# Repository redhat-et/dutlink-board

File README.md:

# jumpstarter
jumpstarter is a project designed to enable generic Hardware in the Loop testability for Edge / embedded designs.

# Software Agent

Should enable standard CI tools and pipeline systems (tekton, gitlab, github, Jenkins, etc...) to integrate with the hardware:
 * Load a device image
 * Reboot
 * Gather logs and wait for finish
 * Return results to the CI system
 * Capture power profile during the whole device lifecycle.

# Hardware Agent
One of the components of the project is an Open Hardware board that bridges the Software and Hardware world
of Edge customers. Enabling them to perform Continous Integration of their Hardware and Software.

It's designed to be mounted on 1U 19" Server racks, in the MiniITX format, and should be connected to an
agent that will perform the control loop on the Device Under Test.

## Features

* USB Storage sharing
  * A storage device can be connected to the Testing host, and then passed down to the DUT
  * USB3.1 (up to 10Gbps) capable
  * USB3.0 and 2.0 capable for backwards compatibility
  * Storage device power cycling

* DUT Power management:
  * ON/OFF, Reset, Reboot
  * Measurement and logging in watts (Integration to Kepler)
  * 5-25V power supply support
  * USB-PD power supply support 5-20V with DUT power negotiation
 
* DUT Control (3.3v I/O)
  * UART Serial port TX/RX (for logging and tracing)
  * 4 customizable control signals
  * RESET signal

# Images of release 1.0.0, on prototyping stage

Yes, we are optimistic with versioning!

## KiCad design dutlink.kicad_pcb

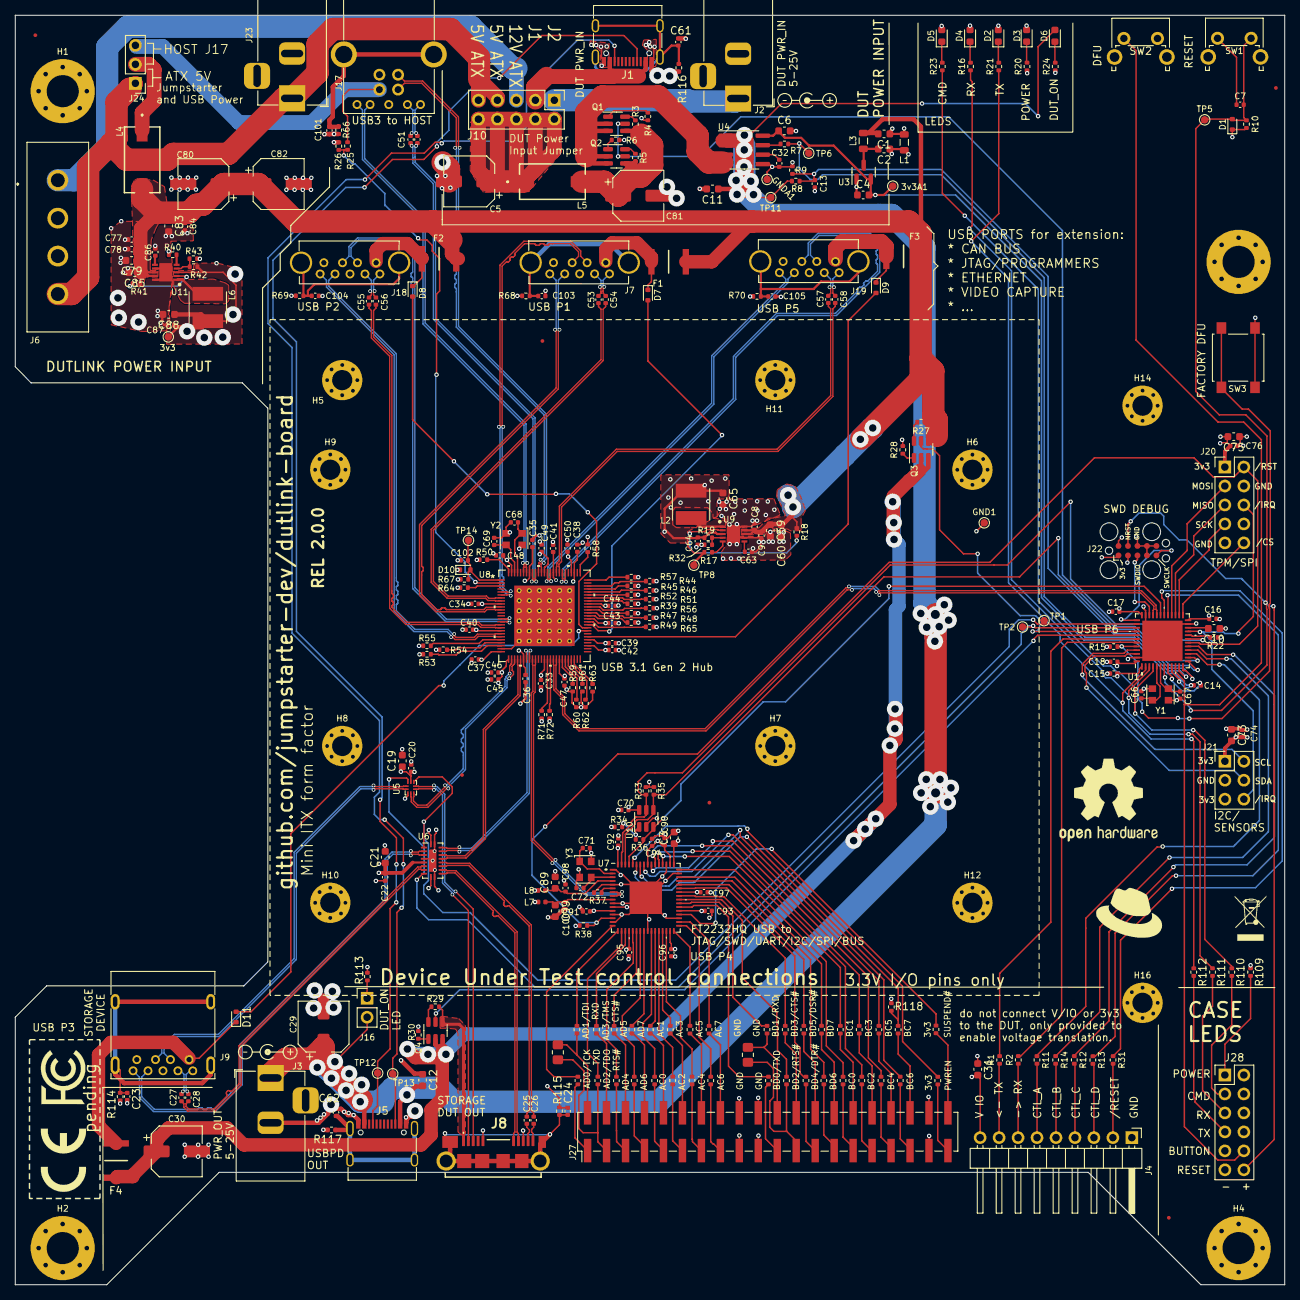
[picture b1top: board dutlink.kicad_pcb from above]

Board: 4 copper layers, 170.0 x 170.0 mm, 320 parts (0 on the bottom side), 273 nets.

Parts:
3v1, 3v3A1: TestPoint; TestPoint_Pad_D1.0mm
C1, C2, C4, C6, C11, C12, C19, C21, C31, C73, C75, C83: 1uF; C_0603_1608Metric
C3: 3.3uF; C_0603_1608Metric
C5, C29, C30, C80, C81, C82: 47uF 32V; CP_Elec_6.3x5.4_Nichicon
C7, C8, C9, C13, C14, C15, C16, C17, C18, C20, C22, C23, C24, C25, C26, C27, C28, C33, C34, C35, C36, C37, C38, C39, C40, C41, C42, C43, C44, C45, C46, C47, C48, C49, C50, C51, C52, C53, C54, C55, C56, C57, C58, C61, C62, C64, C70, C74, C76, C77, C78, C84, C87, C90, C91, C92, C93, C94, C95, C96, C97, C98, C100, C101, C102, C103, C104, C105: 100nF; C_0402_1005Metric
C10, C60, C85: 2.2uF; C_0603_1608Metric
C32: 1nF; C_0402_1005Metric
C59, C65, C79, C88: 22uF; C_0603_1608Metric
C63, C86: 470pF; C_0402_1005Metric
C66, C67, C68, C69: 12pF; C_0402_1005Metric
C71, C72: 27pF; C_0402_1005Metric
C89, C99: 4.7uF; C_0603_1608Metric
D1, D10: 1N4148WT; D_SOD-523
D2, D3, D4, D5, D6: LED; LED_0603_1608Metric
D7, D8, D9, D11: 1N4448WT; D_SOD-523
F1, F2, F3, F4: MF-MSMF125-2
FID1, FID2, FID3, FID4, FID5, FID6: Fiducial; Fiducial_0.5mm_Mask1mm
GND1: TestPoint; TestPoint_Pad_D1.0mm
GNDA1: TestPoint; TestPoint_Pad_D1.0mm
H1, H2, H3, H4: ITX MountingHole; MountingHole_4.3mm_M4_Pad_Via
H5, H6, H7, H8, H9, H10, H11, H12, H14, H16: Board MountingHole; MountingHole_2.7mm_M2.5_Pad_Via
J1, J5: USB_C_Receptacle_PowerOnly_6P; USB_C_Receptacle_G-Switch_GT-USB-7010ASV_fix
J2, J3: Barrel_Jack_MountingPin; BarrelJack_Horizontal
J4: Conn_01x09_Pin; PinHeader_1x09_P2.54mm_Horizontal
J6: Molex 4 Pin Peripheral Power Connector; 3502111
J7, J18, J19: USB3_A; SS-52000-004
J8: Hirose USB3_B_Micro; ZX360DB10P30
J9: USB3_A; USB3_A_Molex_48393-001
J10, J20: SPI/TPM connector; PinHeader_2x05_P2.54mm_Vertical
J16: Conn_01x02_Pin; PinHeader_1x02_P2.54mm_Vertical
J17: USB3_B; Wurth WR-COM USB 3.0 692221030100
J21: I2C connector; PinHeader_2x03_P2.54mm_Vertical
J22: NC; Tag-Connect_TC2050-IDC-FP_2x05_P1.27mm_Vertical
J23: DNM; BarrelJack_Horizontal
J24: Conn_01x03_Pin; PinHeader_1x03_P2.54mm_Vertical
J27: Conn_02x20_Odd_Even; PinHeader_2x20_P2.54mm_Vertical_SMD
J28: 6x2 2.54mm header; PinHeader_2x06_P2.54mm_Vertical
L1, L3: 10uH; L_0805_2012Metric
L2, L6: 1.5uH; LQH5BPB100MT0L
L4, L5: 7427932
L7, L8: 120Ω@100MH; L_0402_1005Metric
Q1, Q2, Q3, Q4: FDC6330L; TSOT-23-6
R1, R2, R7: 50; R_0402_1005Metric
R3, R5, R27, R29: 47k; R_0402_1005Metric
R4, R6, R28, R30: 2k2; R_0402_1005Metric
R8: 2k4 1%; R_0402_1005Metric
R9: 470 1%; R_0402_1005Metric
R10, R15, R17, R18, R19, R22, R33, R34, R35, R39, R40, R41, R44, R45, R46, R47, R48, R49, R55, R56, R57, R58, R65, R67: 10k; R_0402_1005Metric
R11, R12, R13, R14, R31, R73, R74, R75, R76, R77, R78, R79, R80, R81, R82, R83, R84, R85, R86, R87, R88, R89, R90, R91, R92, R93, R94, R95, R96, R97, R98, R99, R100, R101, R102, R103, R104, R105, R106: 100; R_0402_1005Metric
R16, R20, R21, R23, R109, R110, R111, R112: 470; R_0402_1005Metric
R24, R36, R38, R113: 2k; R_0402_1005Metric
R25: 43K; R_0402_1005Metric
R26: 49K9 1%; R_0402_1005Metric
R32, R37, R50: 12k 1%; R_0402_1005Metric
R42: 22k 1%; R_0402_1005Metric
R43: 5k1 1%; R_0402_1005Metric
R51, R52, R53, R54, R59, R60, R61, R62, R63, R71, R72: 200K; R_0402_1005Metric
R64, R118: NC 10k; R_0402_1005Metric
R66, R68, R69, R70, R114, R115, R116, R117: 330; R_0402_1005Metric
R107, R108: NC; R_0805_2012Metric_Pad1.20x1.40mm_HandSolder
SW1, SW2: SW_Push; SW_Tactile_SPST_Angled_PTS645Vx58-2LFS
SW3: SW_Push; SW_SPST_B3S-1000
TP1, TP2, TP5, TP6, TP8, TP11, TP12, TP13, TP14: TestPoint; TestPoint_Pad_D1.0mm
U1: STM32F411CEUx; QFN-48-1EP_7x7mm_P0.5mm_EP5.6x5.6mm
U3: AP2127N-3.3; SOT-23
U4: ACS725LLCTR-05AB-T; SOIC-8_3.9x4.9mm_P1.27mm
U5: TMUXHS221; UQFN-10_1.4x1.8mm_P0.4mm
U6: TMUXHS4212; DHVQFN-20-1EP_2.5x4.5mm_P0.5mm_EP1x3mm
U7: FT2232HQ; QFN-64-1EP_9x9mm_P0.5mm_EP4.35x4.35mm
U8: USB7206CT/KDX; VQFN100_KDX_MCH
U9, U11: MIC23201YML; SON50P300X300X100-11N-D
U10: 93LC56BT-E/OT; SOT-23-6
Y1, Y2: 25 Mhz Crystal +/- 10ppm; Oscillator_SMD_EuroQuartz_XO32-4Pin_3.2x2.5mm
Y3: Cristales 12.000 MHZ 10PF; Oscillator_SMD_EuroQuartz_XO32-4Pin_3.2x2.5mm

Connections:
+1V8: C3.1, C91.2, C92.2, C93.2, U7.12 (VCORE), U7.37 (VCORE), U7.49 (VREGOUT), U7.64 (VCORE)
+3.3V: 3v1.1, C15.1, C16.1, C17.2, C18.1, C19.1, C20.1, C21.1, C22.1, C31.2, C42.1, C43.1, C44.1, C45.1, C46.1, C47.1, C48.1, C49.1, C50.1, C70.2, C73.2, C74.1, C75.2, C76.1, C87.1, C88.1, C90.2, C94.2, C95.2, C96.2, C97.2, D1.1 (K), D2.2 (A), D3.2 (A), D4.2 (A), D5.2 (A), D10.1 (K), J4.9, J20.1, J21.1, J21.5, J22.1, J27.37, J27.38, J28.2, J28.4, J28.6, J28.8, L6.2, L7.1, L8.1, R10.2, R33.1, R34.1, R35.1, R38.2, R40.1, R42.1, R47.2, R48.2, R49.2, R64.2, R67.2, R118.2, SW3.2, U1.1 (VBAT), U1.24 (VDD), U1.36 (VDD), U1.48 (VDD), U5.9 (3V3), U6.1 (RSVD1), U6.6 (VCC), U6.10 (RSVD2), U7.20 (VCCIO), U7.31 (VCCIO), U7.42 (VCCIO), U7.50 (VREGIN), U7.56 (VCCIO), U8.26 (VDD33), U8.43 (VDD33), U8.53 (VDD33), U8.62 (VDD33), U8.67 (VDD33), U8.79 (VDD33), U8.88 (VDD33), U8.99 (VDD33), U10.6 (VCC), U11.3 (SNS)
+3.3VA: 3v3A1.1, C4.2, C6.1, C14.1, U1.9 (VDDA), U3.2 (VO), U4.8 (VCC)
+5V: C1.2, C8.1, C9.1, C59.1, C60.1, C77.1, C78.1, C79.1, C80.1, C82.1, C83.1, C84.1, C85.1, F1.1, F2.1, F3.1, L3.2, L4.2, Q3.4 (S2), R18.1, R27.1, R41.1, U9.8 (SVIN), U9.9 (VIN), U11.8 (SVIN), U11.9 (VIN)
+5VA: C2.2, L3.1, U3.3 (VI)
/BOOT0: R15.1, SW3.1, U1.44 (BOOT0)
/BUTTON: J28.10, SW2.1, U1.10 (PA0)
/CTL_A: R11.1, U1.15 (PA5)
/CTL_B: R14.1, U1.16 (PA6)
/CTL_C: R12.1, U1.17 (PA7)
/CTL_D: R13.1, U1.29 (PA8)
/CURRENT_SENSE: R7.2, TP6.1, U1.11 (PA1)
/DN: U1.32 (PA11), U8.41 (USB2DN_DM6/PRT_DIS_M6)
/DP: U1.33 (PA12), U8.42 (USB2DN_DP6/PRT_DIS_P6)
/FT2232/AC0: R81.1, U7.26 (ACBUS0)
/FT2232/AC1: R82.1, U7.27 (ACBUS1)
/FT2232/AC2: R83.1, U7.28 (ACBUS2)
/FT2232/AC3: R84.1, U7.29 (ACBUS3)
/FT2232/AC4: R85.1, U7.30 (ACBUS4)
/FT2232/AC5: R86.1, U7.32 (ACBUS5)
/FT2232/AC6: R87.1, U7.33 (ACBUS6)
/FT2232/AC7: R88.1, U7.34 (ACBUS7)
/FT2232/AD0: R73.1, U7.16 (ADBUS0)
/FT2232/AD1: R74.1, U7.17 (ADBUS1)
/FT2232/AD2: R75.1, U7.18 (ADBUS2)
/FT2232/AD3: R76.1, U7.19 (ADBUS3)
/FT2232/AD4: R77.1, U7.21 (ADBUS4)
/FT2232/AD5: R78.1, U7.22 (ADBUS5)
/FT2232/AD6: R79.1, U7.23 (ADBUS6)
/FT2232/AD7: R80.1, U7.24 (ADBUS7)
/FT2232/BC0: R97.1, U7.48 (BCBUS0)
/FT2232/BC1: R98.1, U7.52 (BCBUS1)
/FT2232/BC2: R99.1, U7.53 (BCBUS2)
/FT2232/BC3: R100.1, U7.54 (BCBUS3)
/FT2232/BC4: R101.1, U7.55 (BCBUS4)
/FT2232/BC5: R102.1, U7.57 (BCBUS5)
/FT2232/BC6: R103.1, U7.58 (BCBUS6)
/FT2232/BC7: R104.1, R118.1, U7.59 (BCBUS7)
/FT2232/BD0: R89.1, U7.38 (BDBUS0)
/FT2232/BD1: R90.1, U7.39 (BDBUS1)
/FT2232/BD2: R91.1, U7.40 (BDBUS2)
/FT2232/BD3: R92.1, U7.41 (BDBUS3)
/FT2232/BD4: R93.1, U7.43 (BDBUS4)
/FT2232/BD5: R94.1, U7.44 (BDBUS5)
/FT2232/BD6: R95.1, U7.45 (BDBUS6)
/FT2232/BD7: R96.1, U7.46 (BDBUS7)
/FT2232/PWREN: R105.1, U7.60 (~PWREN)
/FT2232/_AC0: J27.9, R81.2
/FT2232/_AC1: J27.10, R82.2
/FT2232/_AC2: J27.11, R83.2
/FT2232/_AC3: J27.12, R84.2
/FT2232/_AC4: J27.13, R85.2
/FT2232/_AC5: J27.14, R86.2
/FT2232/_AC6: J27.15, R87.2
/FT2232/_AC7: J27.16, R88.2
/FT2232/_AD0: J27.1, R73.2
/FT2232/_AD1: J27.2, R74.2, R107.1
/FT2232/_AD2: J27.3, R75.2, R107.2
/FT2232/_AD3: J27.4, R76.2
/FT2232/_AD4: J27.5, R77.2
/FT2232/_AD5: J27.6, R78.2
/FT2232/_AD6: J27.7, R79.2
/FT2232/_AD7: J27.8, R80.2
/FT2232/_BC0: J27.29, R97.2
/FT2232/_BC1: J27.30, R98.2
/FT2232/_BC2: J27.31, R99.2
/FT2232/_BC3: J27.32, R100.2
/FT2232/_BC4: J27.33, R101.2
/FT2232/_BC5: J27.34, R102.2
/FT2232/_BC6: J27.35, R103.2
/FT2232/_BC7: J27.36, R104.2
/FT2232/_BD0: J27.21, R89.2
/FT2232/_BD1: J27.22, R90.2, R108.1
/FT2232/_BD2: J27.23, R91.2, R108.2
/FT2232/_BD3: J27.24, R92.2
/FT2232/_BD4: J27.25, R93.2
/FT2232/_BD5: J27.26, R94.2
/FT2232/_BD6: J27.27, R95.2
/FT2232/_BD7: J27.28, R96.2
/FT2232/_PWREN: J27.39, R105.2
/FT2232/_nSUSPEND: J27.40, R106.2
/FT2232/nSUSPEND: R106.1, U7.36 (~SUSPEND)
/FT2232_DN: U7.7 (DM), U8.35 (USB2DN_DM4/PRT_DIS_M4)
/FT2232_DP: U7.8 (DP), U8.34 (USB2DN_DP4/PRT_DIS_P4)
/FT2232_EECLK: R35.2, U1.13 (PA3), U7.62 (EECLK), U10.4 (CLK)
/FT2232_EECS: R33.2, U1.19 (PB1), U7.63 (EECS), U10.5 (CS)
/FT2232_EEDATA: R36.2, U1.31 (PA10), U7.61 (EEDATA), U10.3 (DI)
/I2C1_SCL: J21.2, U1.45 (PB8)
/I2C1_SDA: J21.4, U1.46 (PB9)
/IRQ_IN: J20.6, J21.6, U1.21 (PB10)
/LED0: R21.1, R112.1, U1.2 (PC13)
/LED1: R16.1, R111.1, U1.3 (PC14)
/LED2: R23.1, R110.1, U1.4 (PC15)
/NRST: C7.2, D1.2 (A), J22.9, J28.12, R10.1, SW1.2, TP5.1, U1.7 (NRST)
/ON_OFF: Q1.5 (G1), Q2.5 (G1), U1.14 (PA4)
/Power/5V_IN: J6.4, J10.7, J10.9, J23.1, J24.1
/Power/5V_IN_: J24.2, L4.1
/Power/12V_IN: J6.1, J10.5
/Power/FBVCORE: R19.2, R32.1, U9.4 (FB)
/Power/FBVCORE3: R42.2, R43.1, U11.4 (FB)
/Power/LVCORE: L2.1, U9.1 (SW)
/Power/LVCORE3: L6.1, U11.1 (SW)
/Power/VBUS_UPSTREAM: J17.1 (VBUS), J24.3, R25.2
/RESET: R31.1, U1.30 (PA9)
/RX: J4.7, R2.1
/RX1: R2.2, U1.43 (PB7)
/SHOST_DN: U5.4 (DA-), U8.28 (USB2DN_DM3/PRT_DIS_M3)
/SHOST_DP: U5.5 (DA+), U8.27 (USB2DN_DP3/PRT_DIS_P3)
/SHOST_SSRXN: U6.18 (B0n), U8.33 (USB3DN_RXDM3)
/SHOST_SSRXP: U6.19 (B0p), U8.32 (USB3DN_RXDP3)
/SHOST_SSTXN: U6.16 (B1n), U8.30 (USB3DN_TXDM3)
/SHOST_SSTXP: U6.17 (B1p), U8.29 (USB3DN_TXDP3)
/SPI2_MISO: J20.5, U1.27 (PB14)
/SPI2_MOSI: J20.3, U1.28 (PB15)
/SPI2_NSS: J20.10, U1.25 (PB12)
/SPI2_SCK: J20.7, U1.26 (PB13)
/SWCLK: J22.5, U1.37 (PA14)
/SWDIO: J22.3, U1.34 (PA13)
/TX: J4.8, R1.1
/TX1: R1.2, U1.42 (PB6)
/USB 3.2 Gen2 front-hub/HOST_DN: J17.2 (D-), U8.90 (USB2UP_DM)
/USB 3.2 Gen2 front-hub/HOST_DP: J17.3 (D+), U8.89 (USB2UP_DP)
/USB 3.2 Gen2 front-hub/HOST_SSRXN: J17.8 (SSRX-), U8.94 (USB3UP_RXDP)
/USB 3.2 Gen2 front-hub/HOST_SSRXP: J17.9 (SSRX+), U8.95 (USB3UP_RXDM)
/USB 3.2 Gen2 front-hub/HOST_SSTXN: C52.1, J17.5 (SSTX-)
/USB 3.2 Gen2 front-hub/HOST_SSTXP: C51.1, J17.6 (SSTX+)
/USB 3.2 Gen2 front-hub/MI2C_CLK: R65.1, U8.61 (PF18)
/USB 3.2 Gen2 front-hub/MI2C_DAT: R64.1, U8.3 (PF31)
/USB 3.2 Gen2 front-hub/MIC_DET: R56.1, U8.66 (PF19)
/USB 3.2 Gen2 front-hub/P1_DN: J7.2 (D-), U8.6 (USB2DN_DM1/PRT_DIS_M1)
/USB 3.2 Gen2 front-hub/P1_DP: J7.3 (D+), U8.5 (USB2DN_DP1/PRT_DIS_P1)
/USB 3.2 Gen2 front-hub/P1_SSRXN: J7.5 (SSRX-), U8.11 (USB3DN_RXDM1)
/USB 3.2 Gen2 front-hub/P1_SSRXP: J7.6 (SSRX+), U8.10 (USB3DN_RXDP1)
/USB 3.2 Gen2 front-hub/P1_SSTXN: C53.1, J7.8 (SSTX-)
/USB 3.2 Gen2 front-hub/P1_SSTXP: C54.1, J7.9 (SSTX+)
/USB 3.2 Gen2 front-hub/P2_DN: J18.2 (D-), U8.15 (USB2DN_DM2/PRT_DIS_M2)
/USB 3.2 Gen2 front-hub/P2_DP: J18.3 (D+), U8.14 (USB2DN_DP2/PRT_DIS_P2)
/USB 3.2 Gen2 front-hub/P2_SSRXN: J18.5 (SSRX-), U8.20 (USB3DN_RXDM2)
/USB 3.2 Gen2 front-hub/P2_SSRXP: J18.6 (SSRX+), U8.19 (USB3DN_RXDP2)
/USB 3.2 Gen2 front-hub/P2_SSTXN: C55.1, J18.8 (SSTX-)
/USB 3.2 Gen2 front-hub/P2_SSTXP: C56.1, J18.9 (SSTX+)
/USB 3.2 Gen2 front-hub/P5_DN: J19.2 (D-), U8.82 (USB2DN_DM5/PRT_DIS_M5)
/USB 3.2 Gen2 front-hub/P5_DP: J19.3 (D+), U8.81 (USB2DN_DP5/PRT_DIS_P5)
/USB 3.2 Gen2 front-hub/P5_SSRXN: J19.5 (SSRX-), U8.87 (USB3DN_RXDM5)
/USB 3.2 Gen2 front-hub/P5_SSRXP: J19.6 (SSRX+), U8.86 (USB3DN_RXDP5)
/USB 3.2 Gen2 front-hub/P5_SSTXN: C57.1, J19.8 (SSTX-)
/USB 3.2 Gen2 front-hub/P5_SSTXP: C58.1, J19.9 (SSTX+)
/USB 3.2 Gen2 front-hub/PRT_CTL1: D7.2 (A), U8.60 (PF17)
/USB 3.2 Gen2 front-hub/PRT_CTL2: D8.2 (A), U8.59 (PF16)
/USB 3.2 Gen2 front-hub/PRT_CTL3: D11.2 (A), U8.58 (PF15)
/USB 3.2 Gen2 front-hub/PRT_CTL5: D9.2 (A), U8.56 (PF13)
/USB 3.2 Gen2 front-hub/SLV_I2C_CLK: R57.1, U8.75 (PF26)
/USB 3.2 Gen2 front-hub/SLV_I2C_DAT: R58.1, U8.76 (PF27)
/USB 3.2 Gen2 front-hub/VBUS_MON_UP: R25.1, R26.2, U8.2 (PF30/VBUS_MON_UP)
/USB 3.2 Gen2 front-hub/XTALI: C69.2, U8.98 (XTALI/CLK_IN), Y2.3
/USB 3.2 Gen2 front-hub/XTALO: C68.2, U8.97 (XTALO), Y2.1
/USB 3.2 Gen2 front-hub/_HOST_SSTXN: C51.2, U8.92 (USB3UP_TXDM)
/USB 3.2 Gen2 front-hub/_HOST_SSTXP: C52.2, U8.91 (USB3UP_TXDP)
/USB 3.2 Gen2 front-hub/_P1_SSTXN: C53.2, U8.8 (USB3DN_TXDM1)
/USB 3.2 Gen2 front-hub/_P1_SSTXP: C54.2, U8.7 (USB3DN_TXDP1)
/USB 3.2 Gen2 front-hub/_P2_SSTXN: C55.2, U8.17 (USB3DN_TXDM2)
/USB 3.2 Gen2 front-hub/_P2_SSTXP: C56.2, U8.16 (USB3DN_TXDP2)
/USB 3.2 Gen2 front-hub/_P5_SSTXN: C57.2, U8.84 (USB3DN_TXDM5)
/USB 3.2 Gen2 front-hub/_P5_SSTXP: C58.2, U8.83 (USB3DN_TXDP5)
/USB 3.2 Gen2 front-hub/nRESET_HUB: C102.2, D10.2 (A), R67.1, TP14.1, U8.1 (RESET_N)
/USB_OEn: TP1.1, U1.38 (PA15), U5.8 (OEn), U6.2 (OEn)
/USB_PW_DUT: Q4.5 (G1), U1.41 (PB5)
/USB_PW_HOST: Q3.5 (G1), U1.40 (PB4)
/USB_SEL: TP2.1, U1.39 (PB3), U5.10 (SEL), U6.9 (SEL)
/USB_STORAGE_MUX/DUT_DN: J8.2 (D-), U5.6 (DB-)
/USB_STORAGE_MUX/DUT_DP: J8.3 (D+), U5.7 (DB+)
/USB_STORAGE_MUX/DUT_SSRXN: C25.1, J8.9 (SSRX-)
/USB_STORAGE_MUX/DUT_SSRXP: C26.1, J8.10 (SSRX+)
/USB_STORAGE_MUX/DUT_SSTXN: J8.6 (SSTX-), U6.12 (C1n)
/USB_STORAGE_MUX/DUT_SSTXP: J8.7 (SSTX+), U6.13 (C1p)
/USB_STORAGE_MUX/STORAGE_DN: J9.2 (D-), U5.2 (D-)
/USB_STORAGE_MUX/STORAGE_DP: J9.3 (D+), U5.1 (D+)
/USB_STORAGE_MUX/STORAGE_SSRXN: J9.5 (SSRX-), U6.4 (A0n)
/USB_STORAGE_MUX/STORAGE_SSRXP: J9.6 (SSRX+), U6.3 (A0p)
/USB_STORAGE_MUX/STORAGE_SSTXN: C27.2, J9.8 (SSTX-)
/USB_STORAGE_MUX/STORAGE_SSTXP: C28.2, J9.9 (SSTX+)
/USB_STORAGE_MUX/VBUS_DUT: J8.1 (VBUS), Q4.4 (S2), R29.1
/USB_STORAGE_MUX/VBUS_STORAGE: C30.1, F4.1, Q3.2 (D2), Q3.3 (D2), Q4.2 (D2), Q4.3 (D2)
/USB_STORAGE_MUX/VBUS_STORAGE_: D11.1 (K), F4.2, J9.1 (VBUS)
/USB_STORAGE_MUX/_DUT_SSRXN: C25.2, U6.14 (C0n)
/USB_STORAGE_MUX/_DUT_SSRXP: C26.2, U6.15 (C0p)
/USB_STORAGE_MUX/_STORAGE_SSTXN: C27.1, U6.8 (A1n)
/USB_STORAGE_MUX/_STORAGE_SSTXP: C28.1, U6.7 (A1p)
/VOUT_SENSE: C13.1, R8.1, R9.2, U1.12 (PA2)
/XTALI: C66.2, U1.5 (PH0), Y1.1
/XTALO: C67.2, U1.6 (PH1), Y1.3
/board_control/CC1: J1.A5 (CC1), J5.A5 (CC1), TP12.1
/board_control/CC2: J1.B5 (CC2), J5.B5 (CC2), TP13.1
/board_control/CTL_A_: J4.6, R11.2
/board_control/CTL_B_: J4.5, R14.2
/board_control/CTL_C_: J4.4, R12.2
/board_control/CTL_D_: J4.3, R13.2
/board_control/J1_VCC: J1.A9 (VBUS), J1.B9 (VBUS), J10.3
/board_control/J2_VCC: J2.1, J10.1
/board_control/RESET_: J4.2, R31.2
/board_control/VCCOUT: C11.1, C12.2, C29.1, D6.2 (A), J3.1, J5.A9 (VBUS), J5.B9 (VBUS), J16.2, R8.2, TP11.1, U4.1 (IP+), U4.2 (IP+)
/board_control/VCCOUT_SW: Q1.2 (D2), Q1.3 (D2), Q2.2 (D2), Q2.3 (D2), U4.3 (IP-), U4.4 (IP-)
/board_control/_CURRENT_SENSE: R7.1, U4.7 (VIOUT)
/board_control/_VCC: C5.1, J10.2, J10.4, J10.6, J10.8, J10.10, L5.1
/nRESET_OUT: J20.2, R38.1, U1.18 (PB0), U7.14 (~RESET)
GND: C1.1, C3.2, C5.2, C7.1, C8.2, C9.2, C10.1, C11.2, C12.1, C15.2, C16.2, C17.1, C18.2, C19.2, C20.2, C21.2, C22.2, C23.2, C24.2, C29.2, C30.2, C31.1, C33.2, C34.2, C35.2, C36.2, C37.2, C38.2, C39.2, C40.2, C41.2, C42.2, C43.2, C44.2, C45.2, C46.2, C47.2, C48.2, C49.2, C50.2, C59.2, C60.2, C61.2, C62.2, C63.2, C64.2, C65.2, C66.1, C67.1, C68.1, C69.1, C70.1, C71.1, C72.1, C73.1, C74.2, C75.1, C76.2, C77.2, C78.2, C79.2, C80.2, C81.2, C82.2, C83.2, C84.2, C85.2, C86.2, C87.2, C88.2, C89.2, C90.1, C91.1, C92.1, C93.1, C94.1, C95.1, C96.1, C97.1, C98.1, C99.2, C100.1, C101.2, C102.1, C103.2, C104.2, C105.2, GND1.1, H1.1, H2.1, H3.1, H4.1, H5.1, H6.1, H7.1, H8.1, H9.1, H10.1, H11.1, H12.1, H14.1, H16.1, J1.A12 (GND), J1.B12 (GND), J2.2, J3.2, J4.1, J5.A12 (GND), J5.B12 (GND), J6.2, J6.3, J7.4 (GND), J7.7 (DRAIN), J8.5 (GND), J8.8 (DRAIN), J9.4 (GND), J9.7 (DRAIN), J17.4 (GND), J17.7 (DRAIN), J18.4 (GND), J18.7 (DRAIN), J19.4 (GND), J19.7 (DRAIN), J20.4, J20.9, J21.3, J22.2, J22.4, J22.6, J22.7, J22.8, J22.10, J23.2, J27.17, J27.18, J27.19, J27.20, J28.9, J28.11, L1.2, R4.2, R6.1, R15.2, R20.1, R22.2, R24.1, R26.1, R28.2, R30.2, R32.2, R37.2, R39.2, R43.2, R44.2, R45.2, R46.2, R50.1, R51.1, R52.1, R53.1, R54.1, R55.1, R56.2, R57.2, R58.2, R59.1, R60.1, R61.1, R62.1, R63.1, R65.2, R66.1, R68.1, R69.1, R70.1, R71.2, R72.2, R109.1, R113.1, R114.1, R115.1, R116.1, R117.1, SW1.1, SW2.2, U1.23 (VSS), U1.35 (VSS), U1.47 (VSS), U1.49 (VSS), U5.3 (GND), U6.5 (GND), U6.11 (GND), U6.20 (GND), U6.21 (GND), U7.1 (GND), U7.5 (GND), U7.10 (AGND), U7.11 (GND), U7.13 (TEST), U7.15 (GND), U7.25 (GND), U7.35 (GND), U7.47 (GND), U7.51 (GND), U7.65 (GND), U8.24 (TESTEN), U8.101 (GND), U9.7 (AGND), U9.10 (PGND), U9.11 (EPAD), U10.2 (GND), U11.7 (AGND), U11.10 (PGND), U11.11 (EPAD), Y1.2, Y1.4, Y2.2, Y2.4, Y3.2, Y3.4
GNDA: C2.1, C4.1, C6.2, C13.2, C14.2, C32.2, GNDA1.1, L1.1, R9.1, U1.8 (VSSA), U3.1 (GND), U4.5 (GND)
unnamed: D2.1 (K), R21.2
unnamed: D3.1 (K), R20.2
unnamed: D4.1 (K), R16.2
unnamed: D5.1 (K), R23.2
unnamed: D6.1 (K), R24.2
unnamed: D7.1 (K), F1.2, J7.1 (VBUS)
unnamed: D8.1 (K), F2.2, J18.1 (VBUS)
unnamed: D9.1 (K), F3.2, J19.1 (VBUS)
unnamed: C61.1, J1.S1 (SHIELD), R116.2
unnamed: C62.1, J5.S1 (SHIELD), R117.2
unnamed: C103.1, J7.10 (SHIELD), R68.2
unnamed: C24.1, J8.11 (SHIELD), R115.2
unnamed: C23.1, J9.10 (SHIELD), R114.2
unnamed: J16.1, R113.2
unnamed: C101.1, J17.10 (SHIELD), R66.2
unnamed: C104.1, J18.10 (SHIELD), R69.2
unnamed: C105.1, J19.10 (SHIELD), R70.2
unnamed: J28.1, R109.2
unnamed: J28.3, R110.2
unnamed: J28.5, R111.2
unnamed: J28.7, R112.2
unnamed: Q1.6 (D1), R3.2
unnamed: Q1.1 (S1), R4.1
unnamed: Q2.6 (D1), R5.2
unnamed: Q2.1 (S1), R6.2
unnamed: Q3.6 (D1), R27.2
unnamed: Q3.1 (S1), R28.1
unnamed: Q4.6 (D1), R29.2
unnamed: Q4.1 (S1), R30.1
unnamed: R22.1, U1.20 (PB2)
unnamed: C10.2, U1.22 (VCAP1)
unnamed: C32.1, U4.6 (BW_SEL)
unnamed: C71.2, U7.2 (OSCI), Y3.1
unnamed: C72.2, U7.3 (OSCO), Y3.3
unnamed: R37.1, U7.6 (REF)
unnamed: C89.1, C98.2, L8.2, U7.4 (VPHY)
unnamed: C99.1, C100.2, L7.2, U7.9 (VPLL)
unnamed: R55.2, U8.21 (CFG_STRAP1)
unnamed: R54.2, U8.22 (CFG_STRAP2)
unnamed: R53.2, U8.23 (CFG_STRAP3)
unnamed: R59.2, U8.44 (PF3)
unnamed: R60.2, U8.45 (PF4)
unnamed: R61.2, U8.46 (PF5)
unnamed: R62.2, U8.47 (PF6)
unnamed: R63.2, U8.48 (PF7)
unnamed: R50.2, U8.100 (RBIAS)
unnamed: R51.2, U8.69 (SPI_CE_N/CFG_NON_REM/PF20)
unnamed: R39.1, U8.68 (SPI_CLK/PF21)
unnamed: R52.2, U8.70 (SPI_D0/CFG_BC_EN/PF22)
unnamed: R46.1, U8.71 (SPI_D1/PF23)
unnamed: R45.1, U8.72 (SPI_D2/PF24)
unnamed: R44.1, U8.73 (SPI_D3/PF25)
unnamed: R49.1, U8.63 (TEST1)
unnamed: R48.1, U8.64 (TEST2)
unnamed: R47.1, U8.65 (TEST3)
unnamed: R72.1, U8.40 (USB3DN_RXDM4)
unnamed: R71.1, U8.39 (USB3DN_RXDP4)
unnamed: R18.2, U9.2 (EN)
unnamed: R17.2, U9.5 (PG)
unnamed: C63.1, U9.6 (SS)
unnamed: R34.2, R36.1, U10.1 (DO)
unnamed: R41.2, U11.2 (EN)
unnamed: R40.2, U11.5 (PG)
unnamed: C86.1, U11.6 (SS)
VCC: C81.1, L5.2, Q1.4 (S2), Q2.4 (S2), R3.1, R5.1
VCORE: C33.1, C34.1, C35.1, C36.1, C37.1, C38.1, C39.1, C40.1, C41.1, C64.1, C65.1, L2.2, R17.1, R19.1, TP8.1, U8.9 (VCORE), U8.18 (VCORE), U8.25 (VCORE), U8.31 (VCORE), U8.38 (VCORE), U8.55 (VCORE), U8.78 (VCORE), U8.85 (VCORE), U8.93 (VCORE), U9.3 (SNS)

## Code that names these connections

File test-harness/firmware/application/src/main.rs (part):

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    use crate::powermeter::*;
    use crate::version;

    type LedCmdType = gpio::PC15<Output<PushPull>>;
    type StorageSwitchType = StorageSwitch<gpio::PA15<Output<PushPull>>, gpio::PB3<Output<PushPull>>,
                                           gpio::PB5<Output<PushPull>>, gpio::PB4<Output<PushPull>>>;
    type CTLPinsType = ctlpins::CTLPins<gpio::PA4<Output<PushPull>>>;
    type DMATransfer = Transfer<Stream0<DMA2>, 0, Adc<ADC1>, PeripheralToMemory, &'static mut [u16; 2]>;

    const DUT_BUF_SIZE: usize = 1024;
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        shell_status: shell::ShellStatus,
        dfu: DFUBootloaderRuntime,

        led_tx: gpio::PC13<Output<PushPull>>,
        led_rx: gpio::PC14<Output<PushPull>>,
        led_cmd: LedCmdType,

        storage: StorageSwitchType,
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    // Local resources to specific tasks (cannot be shared)
    #[local]
    struct Local {
        _button: gpio::PA0<Input>,
        usart_rx: Rx<pac::USART1>,
        usart_tx: Tx<pac::USART1>,
        to_dut_serial: Producer<'static, u8, DUT_BUF_SIZE>,          // queue of characters to send to the DUT
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            .require_pll48clk()
            .freeze();

        // Configure the on-board LED (PC13, blue)
        let gpioa = dp.GPIOA.split();
        let gpiob = dp.GPIOB.split();
        let gpioc = dp.GPIOC.split();

        let mut led_tx = gpioc.pc13.into_push_pull_output();
        let mut led_rx = gpioc.pc14.into_push_pull_output();
        let mut led_cmd = gpioc.pc15.into_push_pull_output();

        led_tx.set_high();
        led_rx.set_high();
        led_cmd.set_high();

        let _button = gpioa.pa0.into_pull_up_input();

        let ctl_pins = ctlpins::CTLPins::new(gpioa.pa5.into_dynamic(),          // ctl_a
                                             gpioa.pa6.into_dynamic(),          // ctl_b
                                             gpioa.pa7.into_dynamic(),          // ctl_c
                                             gpioa.pa8.into_dynamic(),          // ctl_d
                                             gpioa.pa9.into_dynamic(),          // reset
                                             gpioa.pa4.into_push_pull_output()  // power enable
                                            );

        let pins = (gpiob.pb6, gpiob.pb7);
        let usart = Serial::new(
            dp.USART1,
            pins, // (tx, rx)
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        usart_rx.listen();


        let current_sense = gpioa.pa1.into_analog();
        let vout_sense = gpioa.pa2.into_analog();
        let dma = StreamsTuple::new(dp.DMA2);
        let config = DmaConfig::default()
                    .transfer_complete_interrupt(true)
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        let adc_dma_transfer = Transfer::init_peripheral_to_memory(dma.0, adc, first_buffer, None, config);

        let mut storage = StorageSwitch::new(
            gpioa.pa15.into_push_pull_output(), //OEn
            gpiob.pb3.into_push_pull_output(), //SEL
            gpiob.pb5.into_push_pull_output(), //PW_DUT
            gpiob.pb4.into_push_pull_output(), //PW_HOST
        );

        storage.power_off();
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        timer.listen(timer::Event::Update);

        // Pull the D+ pin down to send a RESET condition to the USB bus.
        let mut usb_dp = gpioa.pa12.into_push_pull_output();
        usb_dp.set_low();
        cortex_m::asm::delay(1024 * 50);

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            usb_device: dp.OTG_FS_DEVICE,
            usb_pwrclk: dp.OTG_FS_PWRCLK,
            hclk: clocks.hclk(),
            pin_dm: gpioa.pa11.into_alternate(),
            pin_dp: usb_dp.into_alternate(),
        };

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
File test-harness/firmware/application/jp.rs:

#![no_std]
#![no_main]

use panic_halt as _;

#[rtic::app(device = stm32f4xx_hal::pac, peripherals = true)]
mod app {

    use core::str;
    use stm32f4xx_hal::{
        gpio,
        gpio::{Input, Output, PushPull},
        otg_fs::{UsbBus, UsbBusType, USB},
        pac,
        prelude::*,
        timer,
    };

    use usb_device::{class_prelude::*, prelude::*};

    use usbd_dfu_rt::{DfuRuntimeClass, DfuRuntimeOps};
    use usbd_serial::SerialPort;

    use arrform::{arrform, ArrForm};

    // Resources shared between tasks
    #[shared]
    struct Shared {
        timer: timer::CounterMs<pac::TIM2>,
        usb_dev: UsbDevice<'static, UsbBusType>,
        serial: SerialPort<'static, UsbBusType>,
        serial2: SerialPort<'static, UsbBusType>,
        dfu: DfuRuntimeClass<DFUBootloader>,
    }

    // Local resources to specific tasks (cannot be shared)
    #[local]
    struct Local {
        button: gpio::PA0<Input>,
        led0: gpio::PC13<Output<PushPull>>,
    }

    #[init]
    fn init(ctx: init::Context) -> (Shared, Local, init::Monotonics) {
        static mut USB_BUS: Option<UsbBusAllocator<UsbBusType>,
        > = None;
        static mut EP_MEMORY: [u32; 1024] = [0; 1024];

        let dp = ctx.device;
        let rcc = dp.RCC.constrain();
        let clocks = rcc
            .cfgr
            .use_hse(25.MHz())
            .sysclk(48.MHz())
            .require_pll48clk()
            .freeze();

        // Configure the on-board LED (PC13, blue)
        let gpioa = dp.GPIOA.split();
        //let gpiob = dp.GPIOB.split();
        let gpioc = dp.GPIOC.split();
        let mut led0 = gpioc.pc13.into_push_pull_output();
        let mut led1 = gpioc.pc14.into_push_pull_output();
        let mut led2 = gpioc.pc15.into_push_pull_output();

        led1.set_high();
        led2.set_low();
        
        let button = gpioa.pa0.into_pull_up_input();
        /* 
        let mut ctl_a = gpioa.pa5.into_open_drain_output();
        let mut ctl_b = gpioa.pa6.into_open_drain_output();
        let mut ctl_c = gpioa.pa7.into_open_drain_output();
        let mut ctl_d = gpioa.pa8.into_open_drain_output();
        let mut reset_out = gpioa.pa9.into_open_drain_output();

        let current_sense = gpioa.pa1.into_analog();
        let vout_sense = gpioa.pa2.into_analog();


        let mut usb_store_OEn = gpioa.pa15.into_push_pull_output();
        let mut usb_store_SEL = gpiob.pb3.into_push_pull_output();

        usb_store_OEn.set_low();
        usb_store_SEL.set_low();

        reset_out.set_high();
        ctl_a.set_high();
        ctl_b.set_high();
        ctl_c.set_high();
        ctl_d.set_high();
        */

        let mut timer = dp.TIM2.counter_ms(&clocks);
        timer.start(100.millis()).unwrap();
        // Set up to generate interrupt when timer expires
        timer.listen(timer::Event::Update);

        // BlackPill board has a pull-up resistor on the D+ line.
        // Pull the D+ pin down to send a RESET condition to the USB bus.
        // This forced reset is needed only for development, without it host
        // will not reset your device when you upload new firmware.
        let mut usb_dp = gpioa.pa12.into_push_pull_output();
        usb_dp.set_low();
        cortex_m::asm::delay(1024 * 10);

        let usb_periph = USB {
            usb_global: dp.OTG_FS_GLOBAL,
            usb_device: dp.OTG_FS_DEVICE,
            usb_pwrclk: dp.OTG_FS_PWRCLK,
            hclk: clocks.hclk(),
            pin_dm: gpioa.pa11.into_alternate(),
            pin_dp: usb_dp.into_alternate(),
        };

        unsafe {
            USB_BUS = Some(UsbBus::new(usb_periph, &mut EP_MEMORY));
        }

        let serial = SerialPort::new(unsafe { USB_BUS.as_ref().unwrap() });
        let serial2 = SerialPort::new(unsafe { USB_BUS.as_ref().unwrap() });
        let dfu = DfuRuntimeClass::new(unsafe { USB_BUS.as_ref().unwrap() }, DFUBootloader);

        let usb_dev = UsbDeviceBuilder::new(
            unsafe { USB_BUS.as_ref().unwrap() },
            UsbVidPid(0x2b23, 0x1012),
        )
        .manufacturer("Red Hat Inc. ")
        .product("Jupstarter")
        .serial_number(get_serial_str())
        .device_release(0x0001)
        .self_powered(false)
        .max_power(250)
        .max_packet_size_0(64)
        .build();

        led0.set_high();

        (
            Shared {
                timer,
                usb_dev,
                serial,
                serial2,
                dfu,
            },
            Local {
                button,
                led0,
            },
            // Move the monotonic timer to the RTIC run-time, this enables
            // scheduling
            init::Monotonics(),
        )
    }

    #[task(binds = OTG_FS, shared = [usb_dev, serial, serial2, dfu])]
    fn usb_task(mut cx: usb_task::Context) {
        let usb_dev = &mut cx.shared.usb_dev;
        let serial = &mut cx.shared.serial;
        let serial2 = &mut cx.shared.serial2;
        let dfu = &mut cx.shared.dfu;

        (usb_dev, serial, serial2, dfu).lock(|usb_dev, serial, serial2, dfu| {
            if !usb_dev.poll(&mut [serial, serial2, dfu]) {
                return;
            }
            let mut buf = [0u8; 64];

            match serial.read(&mut buf) {
                Ok(count) if count > 0 => {
                    let af = arrform!(64, "Received {} bytes: {:02x?}\r\n", count, &buf[..count]);
                    serial.write(af.as_bytes()).ok();
                }
                _ => {}
            }
        });
    }

    #[task(binds = TIM2, shared=[timer, dfu], local=[led0])]
    fn timer_expired(mut ctx: timer_expired::Context) {
        // Sends a tick signal to the DFU module
        // Blinks the main LED

        ctx.shared.dfu.lock(|dfu| dfu.tick(100));
        ctx.shared
            .timer
            .lock(|tim| tim.clear_interrupt(timer::Event::Update));
        ctx.local.led0.toggle();
    }

    // Background task, runs whenever no other tasks are running
    #[idle]
    fn idle(_: idle::Context) -> ! {
        loop {
            // Go to sleep
            cortex_m::asm::wfi()
        }
    }

    pub struct DFUBootloader;

    const KEY_STAY_IN_BOOT: u32 = 0xb0d42b89;

    impl DfuRuntimeOps for DFUBootloader {
        const DETACH_TIMEOUT_MS: u16 = 500;
        const CAN_UPLOAD: bool = false;
        const WILL_DETACH: bool = true;

        fn detach(&mut self) {
            cortex_m::interrupt::disable();

            let cortex = unsafe { cortex_m::Peripherals::steal() };

            let p = 0x2000_0000 as *mut u32;
            unsafe { p.write_volatile(KEY_STAY_IN_BOOT) };

            cortex_m::asm::dsb();
            unsafe {
                // System reset request
                cortex.SCB.aircr.modify(|v| 0x05FA_0004 | (v & 0x700));
            }
            cortex_m::asm::dsb();
            loop {}
        }
    }

    /// Returns device serial number as hex string slice.
    fn get_serial_str() -> &'static str {
        static mut SERIAL: [u8; 8] = [b' '; 8];
        let serial = unsafe { SERIAL.as_mut() };

        fn hex(v: u8) -> u8 {
            match v {
                0..=9 => v + b'0',
                0xa..=0xf => v - 0xa + b'a',
                _ => b' ',
            }
        }

        let sn = read_serial();

        for (i, d) in serial.iter_mut().enumerate() {
            *d = hex(((sn >> (i * 4)) & 0xf) as u8)
        }

        unsafe { str::from_utf8_unchecked(serial) }
    }

    /// Return device serial based on U_ID registers.
    fn read_serial() -> u32 {
        let u_id0 = 0x1FFF_7A10 as *const u32;
        let u_id1 = 0x1FFF_7A14 as *const u32;

        unsafe { u_id0.read().wrapping_add(u_id1.read()) }
    }
}

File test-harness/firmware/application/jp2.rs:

//! CDC-ACM serial port example using polling in a busy loop.
#![no_std]
#![no_main]

use panic_halt as _;

use stm32f4xx_hal::interrupt::{SPI5, SPI4};

#[rtic::app(device = stm32f4xx_hal::pac, peripherals = true, dispatchers = [SPI5, SPI4])]
mod app {

    use core::str;
    use stm32f4xx_hal::{
        gpio,
        gpio::{Input, Output, PushPull},
        otg_fs::{UsbBus, UsbBusType, USB},
        prelude::*,
    };

    use usb_device::{class_prelude::*, prelude::*};

    use usbd_dfu_rt::{DfuRuntimeClass, DfuRuntimeOps};
    use usbd_serial::SerialPort;

    use arrform::{arrform, ArrForm};

    use systick_monotonic::{*, fugit::MicrosDurationU64}; // Implements the `Monotonic` trait

    // A monotonic timer to enable scheduling in RTIC
    #[monotonic(binds = SysTick, default = true)]
    type MyMono = Systick<10000>; // 10000 Hz / 0.1 ms granularity

    // Resources shared between tasks
    #[shared]
    struct Shared {
        usb_dev: UsbDevice<'static, UsbBusType>,
        serial: SerialPort<'static, UsbBusType>,
        dfu: DfuRuntimeClass<DFUBootloader>,
    }

    // Local resources to specific tasks (cannot be shared)
    #[local]
    struct Local {
        button: gpio::PA0<Input>,
        led: gpio::PC13<Output<PushPull>>,
        usnd_trigger: gpio::PB9<Output<PushPull>>,
        usnd_echo: gpio::PB8<Input>,
        usnd_start: fugit::Instant<u64,1,10000> ,
    }

    #[init]
    fn init(ctx: init::Context) -> (Shared, Local, init::Monotonics) {
        static mut USB_BUS: Option<UsbBusAllocator<UsbBusType>,
        > = None;
        static mut EP_MEMORY: [u32; 1024] = [0; 1024];

        let mut dp = ctx.device;
        let mut syscfg = dp.SYSCFG.constrain();
        let clocks = dp.RCC.constrain()
            .cfgr
            .use_hse(25.MHz())
            .sysclk(48.MHz())
            .require_pll48clk()
            .freeze();

        let mono = Systick::new(ctx.core.SYST, 48_000_000);

        // Configure the on-board LED (PC13, blue)
        let gpioc = dp.GPIOC.split();
        let gpiob = dp.GPIOB.split();
        let gpioa = dp.GPIOA.split();
        let mut led = gpioc.pc13.into_push_pull_output();
        let button = gpioa.pa0.into_pull_up_input();
        
        let usnd_trigger = gpiob.pb9.into_push_pull_output();
        let mut usnd_echo = gpiob.pb8.into_pull_up_input();

        usnd_echo.make_interrupt_source(&mut syscfg);
        usnd_echo.trigger_on_edge(&mut dp.EXTI, gpio::Edge::RisingFalling);
        usnd_echo.enable_interrupt(&mut dp.EXTI);
        
        // BlackPill board has a pull-up resistor on the D+ line.
        // Pull the D+ pin down to send a RESET condition to the USB bus.
        // This forced reset is needed only for development, without it host
        // will not reset your device when you upload new firmware.
        let mut usb_dp = gpioa.pa12.into_push_pull_output();
        usb_dp.set_low();
        cortex_m::asm::delay(1024 * 10);

        let usb_periph = USB {
            usb_global: dp.OTG_FS_GLOBAL,
            usb_device: dp.OTG_FS_DEVICE,
            usb_pwrclk: dp.OTG_FS_PWRCLK,
            hclk: clocks.hclk(),
            pin_dm: gpioa.pa11.into_alternate(),
            pin_dp: usb_dp.into_alternate(),
        };

        unsafe {
            USB_BUS = Some(UsbBus::new(usb_periph, &mut EP_MEMORY));
        }

        let serial = SerialPort::new(unsafe { USB_BUS.as_ref().unwrap() });
        let dfu = DfuRuntimeClass::new(unsafe { USB_BUS.as_ref().unwrap() }, DFUBootloader);

        let usb_dev = UsbDeviceBuilder::new(
            unsafe { USB_BUS.as_ref().unwrap() },
            UsbVidPid(0x2b23, 0x1012),
        )
        .manufacturer("Red Hat Inc.")
        .product("Jumpstarter")
        .serial_number(get_serial_str())
        .device_release(0x0202) // This is 2.02, you can use a version under the xml declared version
        // for development purposes (allows flashing many times as the version
        // will always be "updateable")
        .self_powered(false)
        .max_power(250)
        .max_packet_size_0(64)
        .build();

        led.set_high();

        // Schedule tasks
        dfu_tick::spawn_after((100 as u64).millis()).unwrap();
        radar::spawn_after((1000 as u64).millis()).unwrap();
        let usnd_start = MyMono::zero();

        (
            Shared {
                usb_dev,
                serial,
                dfu,
            },
            Local {
                button,
                led,
                usnd_trigger,
                usnd_echo,
                usnd_start,
            },
            // Move the monotonic timer to the RTIC run-time, this enables
            // scheduling
            init::Monotonics(mono),
        )
    }

    #[task(binds = EXTI9_5, priority = 2, shared = [serial], local = [led, usnd_echo, usnd_start])]
    fn usnd_echo(mut ctx: usnd_echo::Context) {
        let led = ctx.local.led;
        let usnd_echo = ctx.local.usnd_echo;
        let usnd_start = ctx.local.usnd_start;
        let serial = &mut ctx.shared.serial;

        if usnd_echo.is_high() {
            led.set_low();
            *usnd_start = monotonics::MyMono::now();
        } else {
            let duration = monotonics::MyMono::now() - *usnd_start;
            led.set_high();
            let speed_of_sound = 320; // m/s
            let distance_cm = (duration.to_micros() * speed_of_sound * 100)  / (2 * 1_000_000);
                    
            let af = arrform!(64, "{:?}\n\r", distance_cm);
            serial.lock(|serial| serial.write(af.as_bytes()).ok());
            
            
        }

        usnd_echo.clear_interrupt_pending_bit();
    }

    #[task(binds = OTG_FS, shared = [usb_dev, serial, dfu])]
    fn usb_task(mut cx: usb_task::Context) {
        let usb_dev = &mut cx.shared.usb_dev;
        let serial = &mut cx.shared.serial;
        let dfu = &mut cx.shared.dfu;

        (usb_dev, serial, dfu).lock(|usb_dev, serial, dfu| {
            if !usb_dev.poll(&mut [serial, dfu]) {
                return;
            }
            let mut buf = [0u8; 64];

            match serial.read(&mut buf) {
                Ok(count) if count > 0 => {
                    let af = arrform!(64, "Received {} bytes: {:02x?}\r\n", count, &buf[..count]);
                    serial.write(af.as_bytes()).ok();
                }
                _ => {}
            }
        });
    }

    #[task(shared=[dfu])]
    fn dfu_tick(mut ctx: dfu_tick::Context) {
        dfu_tick::spawn_after((100 as u64).millis()).unwrap();
        ctx.shared.dfu.lock(|dfu| dfu.tick(100));
    }

    #[task(local=[usnd_trigger])]
    fn radar(ctx: radar::Context) {
        radar::spawn_after((100 as u64).millis()).unwrap();
       
        // Trigger the radar measurement
        ctx.local.usnd_trigger.set_high();
        cortex_m::asm::delay(48_000_000/10_000); // 0.01ms up at least
        ctx.local.usnd_trigger.set_low();
    }

    // Background task, runs whenever no other tasks are running
    #[idle]
    fn idle(_: idle::Context) -> ! {
        loop {
            // Go to sleep
            cortex_m::asm::wfi()
        }
    }

    pub struct DFUBootloader;

    const KEY_STAY_IN_BOOT: u32 = 0xb0d42b89;

    impl DfuRuntimeOps for DFUBootloader {
        const DETACH_TIMEOUT_MS: u16 = 500;
        const CAN_UPLOAD: bool = false;
        const WILL_DETACH: bool = true;

        fn detach(&mut self) {
            cortex_m::interrupt::disable();

            let cortex = unsafe { cortex_m::Peripherals::steal() };

            let p = 0x2000_0000 as *mut u32;
            unsafe { p.write_volatile(KEY_STAY_IN_BOOT) };

            cortex_m::asm::dsb();
            unsafe {
                // System reset request
                cortex.SCB.aircr.modify(|v| 0x05FA_0004 | (v & 0x700));
            }
            cortex_m::asm::dsb();
            loop {}
        }
    }

    /// Returns device serial number as hex string slice.
    fn get_serial_str() -> &'static str {
        static mut SERIAL: [u8; 8] = [b' '; 8];
        let serial = unsafe { SERIAL.as_mut() };

        fn hex(v: u8) -> u8 {
            match v {
                0..=9 => v + b'0',
                0xa..=0xf => v - 0xa + b'a',
                _ => b' ',
            }
        }

        let sn = read_serial();

        for (i, d) in serial.iter_mut().enumerate() {
            *d = hex(((sn >> (i * 4)) & 0xf) as u8)
        }

        unsafe { str::from_utf8_unchecked(serial) }
    }

    /// Return device serial based on U_ID registers.
    fn read_serial() -> u32 {
        let u_id0 = 0x1FFF_7A10 as *const u32;
        let u_id1 = 0x1FFF_7A14 as *const u32;

        unsafe { u_id0.read().wrapping_add(u_id1.read()) }
    }
}

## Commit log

2023-07-14 start directory structure
2023-07-14 Working on firmware
2023-07-14 Add missing cargo config
2023-07-17 Basic shell commands on ttyACM0
2023-07-18 Increment USB line pull time at boot
2023-07-18 Refactoring out into modules
2023-07-18 Continued refactor into modules
2023-07-19 Only one serial port, cleanups and refactors
    Two serial ports don't seem to work properly even on an STM32F412,
    so staying with 1 serial port for now.
    Cleanups and refactor of commands in the shell.
2023-07-19 reset serial and add console mode
2023-07-20 Avoid no_std bug reporting test missing
2023-07-20 Split Uart RX and TX, increase buffers, stop escaping in console mode
    Splitting RX and TX side of uart object avoids locking, and
    the separate handles can be used in separate tasks locally.
    Escaping of \n\r\w etc should not be handled in console mode
2023-07-20 Fix shell commands in help
2023-07-21 Switch back to stm32f411 for now
2023-07-21 Add debug target, sometimes needed
2023-07-21 Add basic power metering and ADC streaming via DMA
2023-07-21 Implement set commands
2023-07-24 Pin control via SET
2023-07-25 Upload to LVFS
2023-07-25 HiZ control pins on power off
2023-07-25 Encapsulate power and filter on it's own modules
2023-07-25 Fix product name
2023-07-26 Allow power metering on the console
2023-07-26 Compile in VERSION from makefile
    This avoids the issue of the version being spread across a Makefile,
    the xml description of the driver, and the usb descriptor in main.rs
2023-07-26 Add about command and fix meter bug
2023-07-26 Add missing files
2023-07-27 Make rust-analyzer happier for missing env vars
2023-07-27 Move directories to top level
    This commit handles the separation of repositories
2023-08-08 Add configuration area in flash
    Additional space has been reserved between bootloader
    and firmware application for configuration.
    Configuration allows storage, name and tags.
2023-08-08 If config flash format is incompatible erase
2023-09-07 Allow a setting for a separate USB console
    The Orin AGX board provides access to the kernel and UEFI consoles
    via USB only today, not via the 40-pin header.
    To allow jumpstarter accessing systems like these, we can enable
    the jumpstarter software to look-up for a separate usb console
    on the host.
    i.e. with an Orin AGX board we could store:
2023-09-15 Store the usb_console config in the right attribute
2023-10-10 Implement power-on/power-of basic programmable profiles
    This enables the ability to toggle pins during bootup or
    to interace with power control on boards.
2023-10-10 Introduce power rescue profile
2023-10-10 Add container shell for building
2023-10-10 Build in containers
2023-10-10 Fix bug printing power_rescue
2023-10-13 Fix bug for empty power config
2023-11-08 README: fix image links
2023-11-22 WIP 1.1
2023-12-01 Started routing USB3 diff pairs
2023-12-05 Routing and several design fixes
2023-12-09 Continued routing
2023-12-18 Almost ready 2.0.0
2023-12-19 REL 1.1.0
2024-01-05 Reorganized repo with rename to dutlink 1.1.0
2024-01-05 Remove firmware workflows
2024-01-05 removed bom output
2024-02-02 2.0.0 release
